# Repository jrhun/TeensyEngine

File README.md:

# TeensyEngine

TeensyEngine is primarily the software I use for my Totem Pole - named *The Orb*. 

Included in this repository is a description of both the hardware and software features, including the MCAD/ECAD designs for everything.
It includes an emulator that's using OpenFrameworks for display and UI control, allowing easy testing and development.

<details>
<summary>  The Orb in the wild 
</summary>

</details>

## Contents 
- [About](#about)
- [Features](#features)
- [Hardware](#hardware)
- [Software](#software)
- [Credit](#credit)

## About
I took ~2000 LED lights and carefully shoved them inside a polycarbonate ball that was then placed on top of a stick and hooked up to a microprocessor and battery pack. Shockingly, it worked quite well! I use it as a Totem Pole for music festivals, come say hi if you see it!

This has been a multiyear endeavor  that I've slowly added more and more features to. It's the 4th iteration of the hardware including LEDs and controller/battery box. The first version was a couple of LEDs taped down inside two salad bowls - [how far this project has come since then!](buildLog/README.md#previous-versions)

Just a heads up - I'm an almost completely self taught programmer/3d modeler/electronics designer, there is a level of *jank* at times that should be expected to come of that, but overall I've been very pleased with the outcome! 
I will gladly take any suggestions or tips to improve my work, please comment any suggestions!

## Features

- 25+ different patterns with the ability to change the colour palette being used for most patterns!
- Custom global blur/fade/glitter effects that can run on top of any pattern
- Text overlay onto patterns with the ability to enter custom text using the controller
- LCD Screen for changing settings/patterns + showing battery voltage and power usage
- Current sensor for monitoring power usage
- Encoder + buttons for navigating the UI
- An accelerometer (because why not)
- Microphone input 
- Wireless compatibility with NRF24L01 or ESP-01

<details open>
<summary> Videos of patterns on the hardware </summary>

https://user-images.githubusercontent.com/25134458/209674595-40512c94-f8f8-4173-94cc-6f29fc267113.mp4

https://user-images.githubusercontent.com/25134458/209741537-4713a7b6-7f0b-4868-8ff8-e278ab186450.mp4

https://user-images.githubusercontent.com/25134458/209743201-d97811d2-97b1-4fea-91a2-2c5a3d3df347.mp4

</details>

## Hardware
Some photos of the completed project can be found [here](buildLog/README.md).
I made a custom circuit board for connecting everything up along with a daughter board for [powering](#Power) the LEDs and providing the data through a CAT5 cable. 

#### Processor
A teensy 4.0 is the heart of the project, providing plenty of raw power to overcome my inefficient coding and push out LEDs while controlling  a UI.

#### Accessories
- Microphone - I can't remember what I'm using, one of the Sparkfun electret autogain boards. 
- NRF24l01 - used to connect wirelessly to LED headbands - allows you to change the patterns/brightness/colour of the headbands!
- ESP-01 - pins to connect to an ESP are broken out but not yet implemented
- ACS712 current sensor in series with the LEDs to measure power usage
- MSGEQ7 - the pinout is there but I haven't ended up using it yet
- ILI9341 colour TFT display 240x320 
- MPU9250 accelerometer

If trying to make this project, please confirm the pinout matches for the display and accelerometer! I got caught out and assumed they were the same for the two almost identical accelerometers I had, then needed to edit the circuit board. Also the linear regulator for the processor 5V line got way too hot so I changed it for a small buck convertor that (roughly) matched it's footprint. To be honest the circuit board could be redone with a teensy 4.1, as soldering the pogo pins to connect to the back of the teensy 4.0 was very tedious. 

#### Lights
Custom 3d printed scaffolding for strips of SK6805-2427 RGB LEDs, to hold them in a spherical shape inside a polycarbonate ball 25cm in diameter. They're held slightly back from the inside of the sphere to help diffuse the lights nicely. The scaffolding press fits together and tolerances were set for my 3d printer - YUMV. They're also held in place under slight compression from the globe. The LED strips are arranged as 30 to a strip with an offset pattern to reduce crowding at the poles, allowing for an effective resolution of 32H x 64W. See the [build details](buildLog/README.md#leds) for photos. 

The lights are from [Aliexpress](https://www.aliexpress.com/item/32818340106.html?spm=a2g0o.order_list.order_list_main.358.679f1802EQyb32), and were chosen for their high density (120/M, 8.33mm pitch) and thin strips (6mm width). 
Lights with a smaller pitch and thinner strip were outrageously expensive at the time I was purchasing LEDs, but have since come down in price somewhat... Version 5 [TBC](https://www.aliexpress.com/item/1005003798198621.html?spm=a2g0o.productlist.main.1.1ec91845yMUVny&algo_pvid=75d3a123-2f4a-48b9-b82f-fbbad28e56ed&algo_exp_id=75d3a123-2f4a-48b9-b82f-fbbad28e56ed-0&pdp_ext_f=%7B%22sku_id%22%3A%2212000028080815414%22%7D&pdp_npi=2%40dis%21AUD%2140.15%2126.11%21%21%21%21%21%40211bf14716719782508633629d0742%2112000028080815414%21sea&curPageLogUid=63plojRdJNp2)?

#### Power
The whole thing is powered by 4x 18650 batteries, I usually carry a spare set of 4x batteries for each night that it's used which usually lasts the night through.
There's a step-down converter in the controller providing 5V for the teensy and accessories. The full battery voltage is sent up to the LEDs where there is a separate step-down convertor. The benefit of the two power supplies is efficiency and stability, having a separate power source for the controller means its voltage doesn't dip when the LEDs draw a bunch of power. It also means I can provide much more power than *most* USB powerbanks, although I do want to try sending 20v from a 100w USB-C powerbank to the LEDs. Further details in the [build section.](buildLog/README.md#power)

## Software
The software include a basic emulator that runs the same UI and pattern software using OpenFrameworks to display the LEDs. 

<details open>
  <summary>Videos of the controller</summary>
 
  https://user-images.githubusercontent.com/25134458/209736586-94fa050d-8a2f-43fb-920e-38acb0f2c6ba.mp4
  
  https://user-images.githubusercontent.com/25134458/209676572-e61da54b-b9a8-4b95-bfd1-fcbd3a2c399e.mp4
  
</details>

### UI Pages
I've tried to organise the UI controls into roughly similar pages. The current battery voltage and current draw is shown in to top right corner, and the current FastLED FPS reading in the bottom right corner. The name of the totem is on the top of the screen, then the current page and a depiction of what page you're on. Joystick left/right changes the page, and up and down to select a setting. Hovering over a setting allows you to change a value with the encoder, or for some settings such as picking a pattern or palette you can press the joystick to enter a menu for that listing options. 

- **Pattern controls**
  - Select desired patterns from the list of patterns
  - Change overall brightness
  - Select a tempo + tap tempo
  - Change the tempo oscillator between square/ramp/sine etc...
  - Trigger ability to change a patterns settings (e.g. trigger different settings for a pattern without making a complete new one, see )
- **Colour controls**
  - Change current palette with a palette preview option
  - Blend amount when changing palette  over - quick or slow blend
  - Change how fast colours from a palette are cycled through
- **Text/FX controls**
  - Add transparent or opaque text over any pattern, or just blink text 
  - Text scroll speed
  - Select the text from a list or enter custom text (12 char max only!)
  - Global blur/fade/glitter effects
- **Wireless controls**
  - Control the wireless headbands I made using NRF24L01 communication
  - Change the pattern/colour/brightness of headbands in range
- **General settings**
  - LCD Backlight/Dither/Colour temp/Accelerometer/Save/load settings

### Adding a new pattern
The basic format for a pattern is a class inheriting from the `_Pattern` class, and should have the name for the pattern passed to it.

A `drawFrame()` function should be provided that is called to run the pattern. You can set the delay in msec for when to draw the next frame by the value you return. It also provides functions that are automatically called when starting or stopping a pattern, and a trigger option. Helper functions for drawing to the LED matrix are in the `gfx` class from `Graphics.h`. Try using `gfx.getColour(uint8_t offset)` for colours because this links in to the palette system. 

Include the code for a new pattern in `src/patterns/PatternController.h`, then add it as a member to the `PatternController` class and include it in the `patternList`
<details>
<summary>Example pattern</summary>
  
#### Blink all LEDs on/off
  ```
  class PatternBlink : public _Pattern {
  public:
    PatternBlink() : _Pattern("Blink") {}
    uint8_t drawFrame() {
      if (++count > 100) {
        count = 0;
        flip != flip;
      }
      if (flip) gfx.fill(gfx.getColour());
      else      gfx.fill(CRGB::Black);
      return returnVal; //default 10, 1000/10 = 100fps
    }
    uint8_t count = 0;
    bool flip = false;
  };
  ```
</details>

## Arduino code
The Teensyduino core was used for compiling and uploading.
`Graphics.h` does all the heavy lifting for helper functions. 

Arduino libraries used:
- [ILI9341_t3n](https://github.com/KurtE/ILI9341_t3n)
- [Encoder](https://github.com/PaulStoffregen/Encoder/blob/master/Encoder.h) from Paul Stroffregen
- [MPU9250](https://github.com/kriswiner/MPU9250) from kriswiner
- [FastLED](https://github.com/FastLED/FastLED)
- [Teensy ADC](https://github.com/pedvide/ADC)
- [RF24](https://github.com/nRF24/RF24)

## PC Emulator 

https://user-images.githubusercontent.com/25134458/209675905-0a1664af-fdfa-492f-b072-93c58537c89a.mp4

#### Requirements 
OpenFrameworks 0.10.1 was used for the graphics, with the ofxGui addon.

Visual Studio 2019 was used for compiling.
At one point I had it compiling on Mac XCode, but I haven't checked if that still works in a while.

<details open>
  <summary>The emulator has keyboard controls for the UI:</summary>
  
  - WASD: joystick up/left/down/right
  - Q/E: encoder rotate clockwise/counter clockwise
  - F: joystick press 
  - space: separate trigger, triggers effect on certain patterns (calls Pattern::Trigger())
  - Home/End/Del/PgDown: change pitch/roll level to emulate accelerometer changes
  - I: add random impulse to accelerometer data
  - 1 through 7: change beat type (RAMP, INVERSE_RAMP, TRIANGLE, SQUARE, SIN, TRIGGER, GATE, AUDIO, AUDIO_AVG, OFF)
</details>

## To-do list
- [ ] Add more photos of the completed totem to the build log
- [ ] More patterns
- [ ] Accelerometer fluid simulation - I've had multiple attempts but it just doesn't look right, a little beyond my abilities currently!
- [ ] More audio responsive patterns/improving audio code
- [ ] More patterns to respond to accelerometer 
- [ ] Make better use of global effects - the LEDs are double buffered but this is only really used for text currently
- [ ] Rotatable 3d view of the totem in the emulator rather than displaying as a flat 2d matrix

## Credit 
This project has taken inspiration from countless different sources. Please see [CONTRIBUTIONS.md](CONTRIBUTIONS.md) for full details.

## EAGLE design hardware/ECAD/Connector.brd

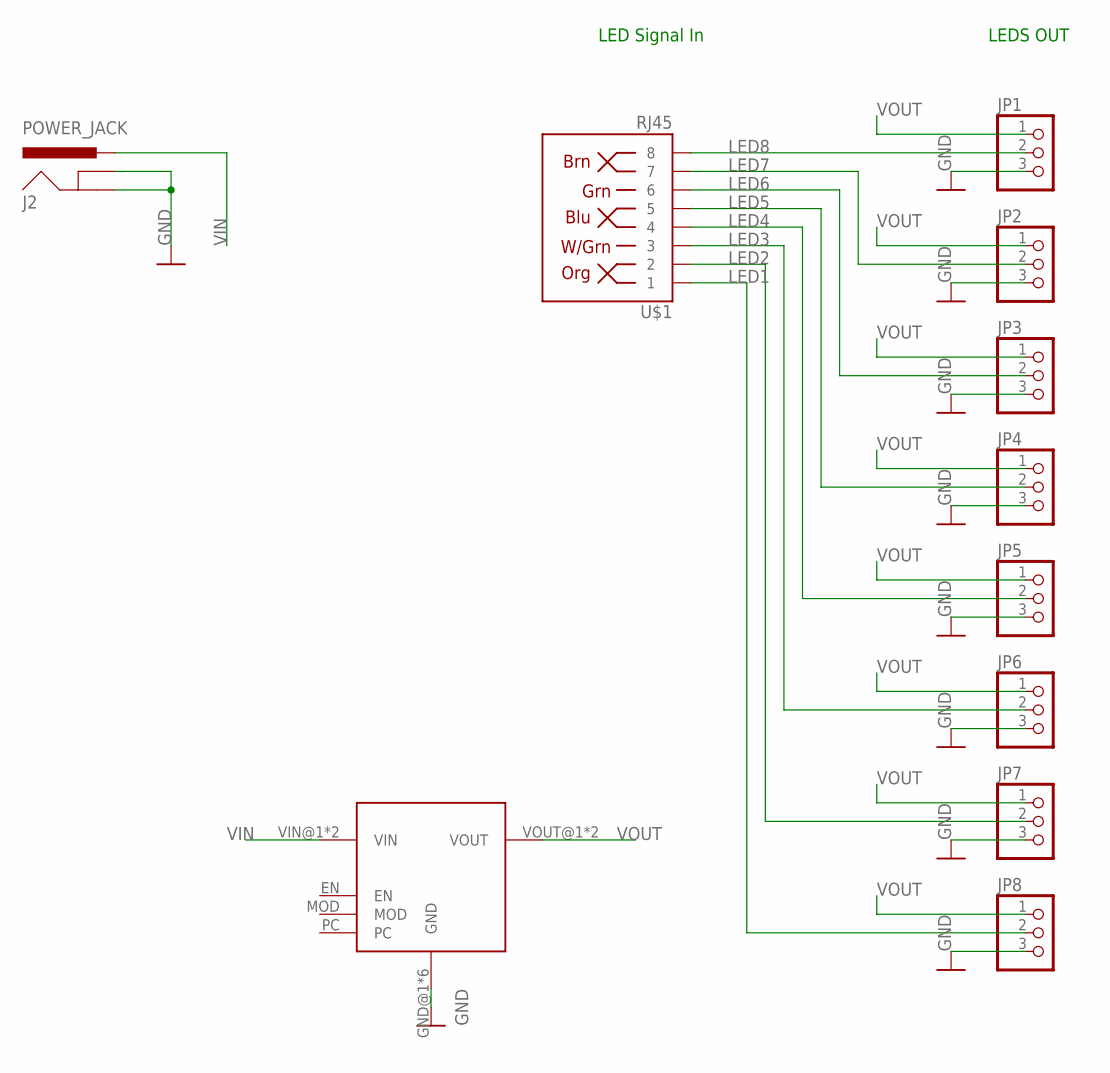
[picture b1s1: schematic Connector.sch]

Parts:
J2: POWER_JACK; POWER_JACK_PTH
JP1, JP2, JP3, JP4, JP5, JP6, JP7, JP8: PINHD-1X3; 1X03
U$1: RJ45; RJ45_WINGS
U$2: 5V-15A-VOLTAGE_CONVERTER; D24V150F

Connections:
GND: J2.GND, J2.GNDBREAK, JP1.3, JP2.3, JP3.3, JP4.3, JP5.3, JP6.3, JP7.3, JP8.3, U$2.GND@1 (GND), U$2.GND@2 (GND), U$2.GND@3 (GND), U$2.GND@4 (GND), U$2.GND@5 (GND), U$2.GND@6 (GND)
LED1: JP8.2, U$1.1
LED2: JP7.2, U$1.2
LED3: JP6.2, U$1.3
LED4: JP5.2, U$1.4
LED5: JP4.2, U$1.5
LED6: JP3.2, U$1.6
LED7: JP2.2, U$1.7
LED8: JP1.2, U$1.8
VIN: J2.PWR, U$2.VIN@1 (VIN), U$2.VIN@2 (VIN)
VOUT: JP1.1, JP2.1, JP3.1, JP4.1, JP5.1, JP6.1, JP7.1, JP8.1, U$2.VOUT@1 (VOUT), U$2.VOUT@2 (VOUT)

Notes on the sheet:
LED Signal In
LEDS OUT

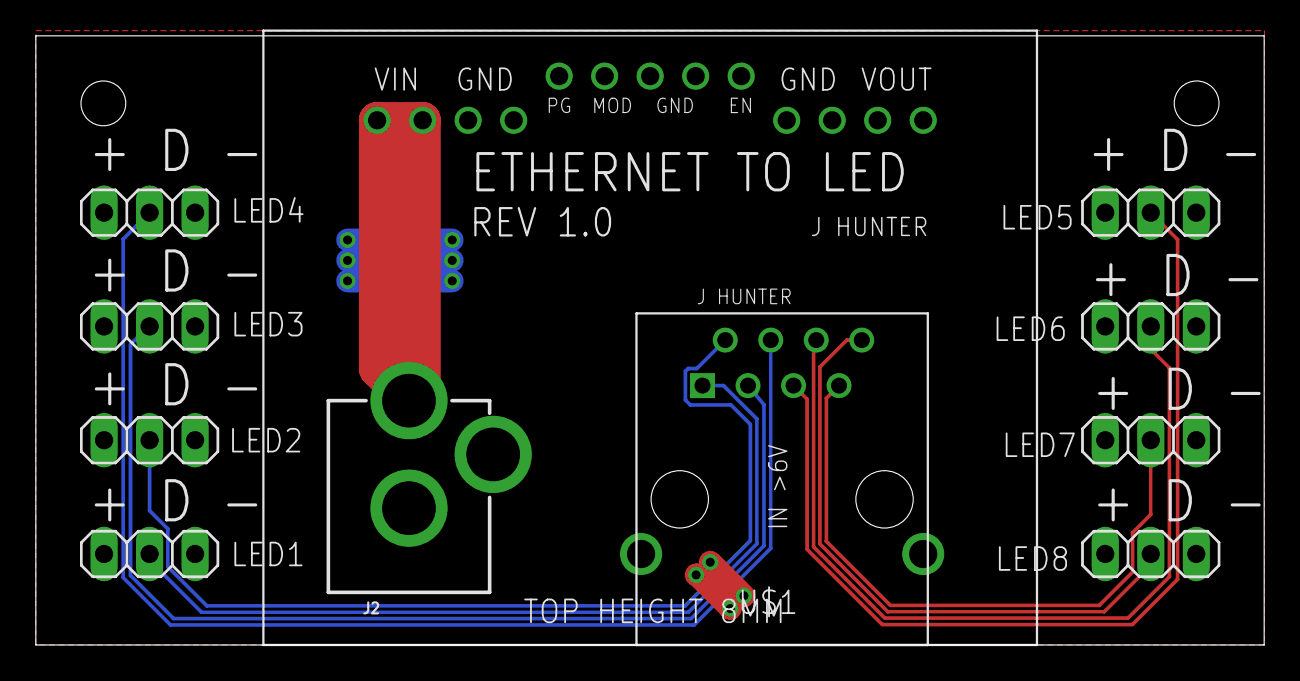
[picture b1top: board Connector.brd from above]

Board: 2 copper layers, 68.6 x 34.0 mm, 11 parts (0 on the bottom side), 11 nets.

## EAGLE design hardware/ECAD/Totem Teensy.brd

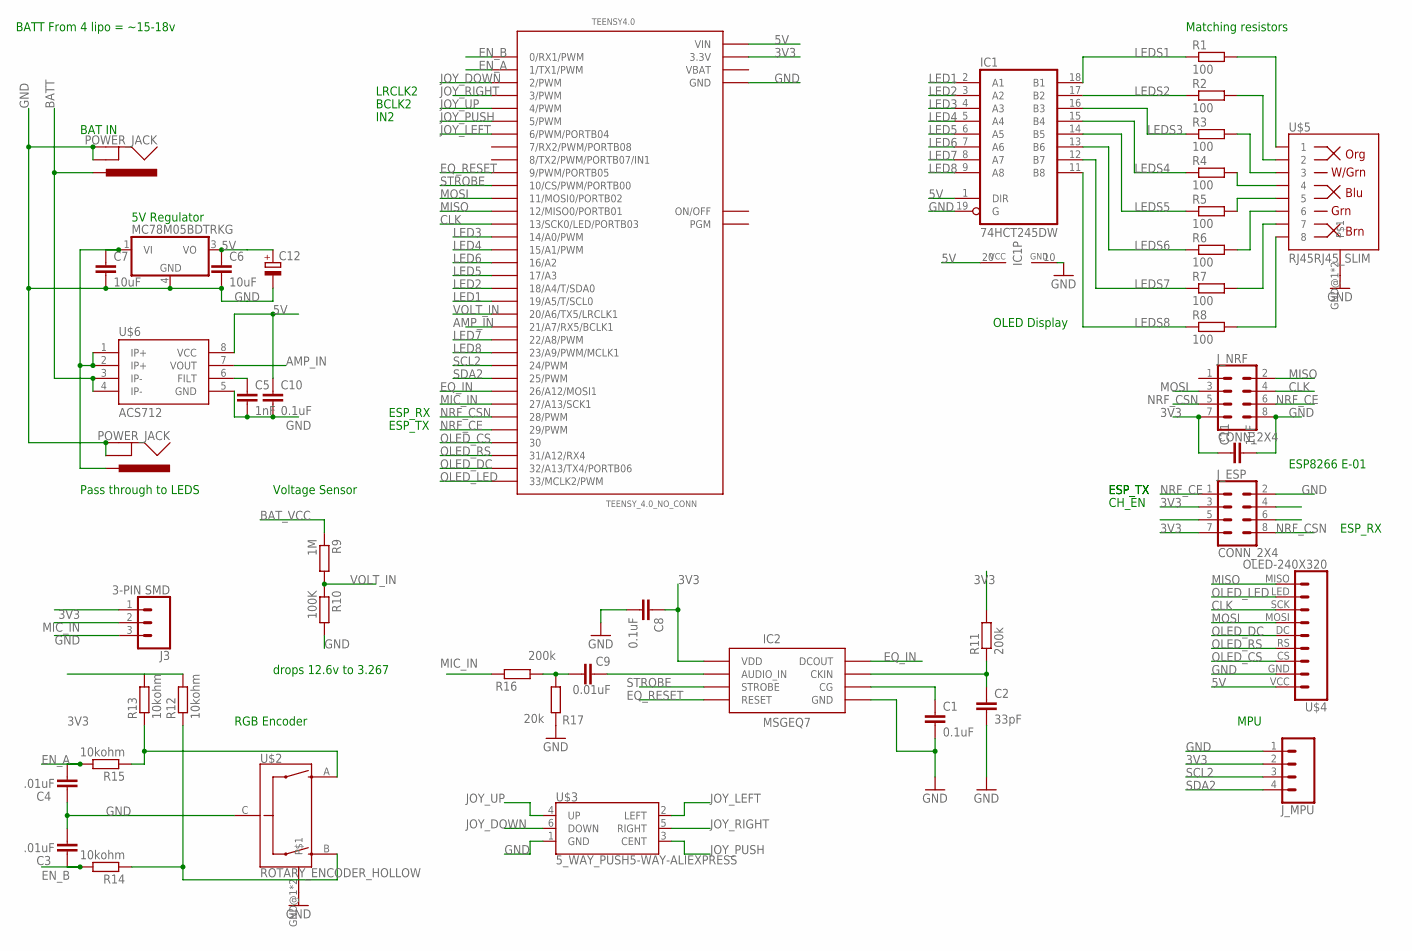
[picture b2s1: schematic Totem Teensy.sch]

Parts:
C1, C8, C10: 0.1uF; C1206
C2: 33pF; C1206
C3, C4: .01uF; C1206
C5: 1nF; C1206
C6, C7: 10uF; C1206
C9: 0.01uF; C1206
C11: 1uF; C1206
C12: CPOL-EUTT2D5L; TT2D5L
IC1: 74HCT245DW; SO20W
IC2: MSGEQ7DIP; DIL08
IC3: MC78M05BDTRKG; DPACK_3
J1, J7: POWER_JACK; POWER_JACK_PTH
J3: 3-PIN SMD; JST-3-SMD
J_ESP: CONN_2X4; 2X4
J_MPU: CONN_04; 1X04
J_NRF: CONN_2X4; 2X4
R1, R2, R3, R4, R5, R6, R7, R8: 100; R1206
R9: 1M; M1206
R10: 100K; M1206
R11, R16: 200k; R1206
R12, R13, R14, R15: 10kohm; R1206
R17: 20k; R1206
TEENSY4.0: TEENSY_4.0_NO_CONN; TEENSY_4.0
U$2: ROTARY_ENCODER_HOLLOW; HOLLOW_ENCODER30R
U$3: 5_WAY_PUSH5-WAY-ALIEXPRESS; 5-WAY_PTH2
U$4: OLED-240X320; OLED_240X320
U$5: RJ45RJ45_SLIM; RJ45_SLIM
U$6: ACS712; SO08

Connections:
3V3: C8.1, C11.1, IC2.1 (VDD), J3.1, J_ESP.3, J_ESP.7, J_MPU.2, J_NRF.7, R11.2, R12.2, R13.2, TEENSY4.0.3.3@0 (3.3V), TEENSY4.0.3.3@1 (3.3V)
5V: C6.1, C10.1, C12.+, IC1.1 (DIR), IC1.20 (VCC), IC3.3 (VO), TEENSY4.0.VIN, U$4.VCC, U$6.8 (VCC)
AMP_IN: TEENSY4.0.21/A7 (21/A7/RX5/BCLK1), U$6.7 (VOUT)
BATT: J1.PWR, U$6.3 (IP-), U$6.4 (IP-)
BAT_VCC: C7.1, IC3.1 (VI), J7.PWR, R9.1, U$6.1 (IP+), U$6.2 (IP+)
CLK: J_NRF.4, TEENSY4.0.13 (13/SCK0/LED/PORTB03), U$4.SCK (CLK)
EN_A: C4.1, R15.2, TEENSY4.0.1 (1/TX1/PWM)
EN_B: C3.2, R14.2, TEENSY4.0.0 (0/RX1/PWM)
EQ_IN: IC2.3 (DCOUT), TEENSY4.0.26 (26/A12/MOSI1)
EQ_RESET: IC2.7 (RESET), TEENSY4.0.9 (9/PWM/PORTB05)
GND: C1.2, C2.2, C3.1, C4.2, C5.2, C6.2, C7.2, C8.2, C10.2, C11.2, C12.-, IC1.10 (GND), IC1.19 (G), IC2.2 (GND), IC3.4 (GND), J1.GND, J1.GNDBREAK, J3.3, J7.GND, J7.GNDBREAK, J_ESP.2, J_MPU.1, J_NRF.8, R10.2, R17.2, TEENSY4.0.GND@0 (GND), TEENSY4.0.GND@1 (GND), TEENSY4.0.GND@2 (GND), U$2.C, U$2.GND@1, U$2.GND@2, U$3.1 (GND), U$4.GND, U$5.GND@1, U$5.GND@2, U$6.5 (GND)
JOY_DOWN: TEENSY4.0.2 (2/PWM), U$3.6 (DOWN)
JOY_LEFT: TEENSY4.0.6 (6/PWM/PORTB04), U$3.2 (LEFT)
JOY_PUSH: TEENSY4.0.5 (5/PWM), U$3.3 (CENT)
JOY_RIGHT: TEENSY4.0.3 (3/PWM), U$3.5 (RIGHT)
JOY_UP: TEENSY4.0.4 (4/PWM), U$3.4 (UP)
LED1: IC1.2 (A1), TEENSY4.0.19/A5 (19/A5/T/SCL0)
LED2: IC1.3 (A2), TEENSY4.0.18/A4 (18/A4/T/SDA0)
LED3: IC1.4 (A3), TEENSY4.0.14/A0 (14/A0/PWM)
LED4: IC1.5 (A4), TEENSY4.0.15/A1 (15/A1/PWM)
LED5: IC1.6 (A5), TEENSY4.0.17/A3
LED6: IC1.7 (A6), TEENSY4.0.16/A2
LED7: IC1.8 (A7), TEENSY4.0.22/A8 (22/A8/PWM)
LED8: IC1.9 (A8), TEENSY4.0.23/A9 (23/A9/PWM/MCLK1)
LEDS1: IC1.18 (B1), R1.1
LEDS2: IC1.17 (B2), R2.1
LEDS3: IC1.16 (B3), R3.1
LEDS4: IC1.15 (B4), R4.1
LEDS5: IC1.14 (B5), R5.1
LEDS6: IC1.13 (B6), R6.1
LEDS7: IC1.12 (B7), R7.1
LEDS8: IC1.11 (B8), R8.1
MIC_IN: J3.2, R16.2, TEENSY4.0.27 (27/A13/SCK1)
MISO: J_NRF.2, TEENSY4.0.12 (12/MISO0/PORTB01), U$4.MISO
MOSI: J_NRF.3, TEENSY4.0.11 (11/MOSI0/PORTB02), U$4.MOSI
unnamed: R1.2, U$5.8 (1)
unnamed: R2.2, U$5.7 (2)
unnamed: R4.2, U$5.5 (4)
unnamed: R3.2, U$5.6 (3)
unnamed: R5.2, U$5.4 (5)
unnamed: R6.2, U$5.3 (6)
unnamed: R7.2, U$5.2 (7)
unnamed: R8.2, U$5.1 (8)
unnamed: C9.2, R16.1, R17.1
unnamed: C9.1, IC2.5 (AUDIO_IN)
unnamed: C5.1, U$6.6 (FILT)
unnamed: R13.1, R15.1, U$2.A
unnamed: R12.1, R14.1, U$2.B
unnamed: C2.1, IC2.8 (CKIN), R11.1
unnamed: C1.1, IC2.6 (CG)
NRF_CE: J_ESP.1, J_NRF.6, TEENSY4.0.29 (29/PWM)
NRF_CSN: J_ESP.8, J_NRF.5, TEENSY4.0.28 (28/PWM)
OLED_CS: TEENSY4.0.30, U$4.CS
OLED_DC: TEENSY4.0.32 (32/A13/TX4/PORTB06), U$4.DC
OLED_LED: TEENSY4.0.33 (33/MCLK2/PWM), U$4.LED
OLED_RS: TEENSY4.0.31 (31/A12/RX4), U$4.RS
SCL2: J_MPU.3, TEENSY4.0.24 (24/PWM)
SDA2: J_MPU.4, TEENSY4.0.25 (25/PWM)
STROBE: IC2.4 (STROBE), TEENSY4.0.10 (10/CS/PWM/PORTB00)
VBAT: TEENSY4.0.VBAT
VOLT_IN: R9.2, R10.1, TEENSY4.0.20/A6 (20/A6/TX5/LRCLK1)

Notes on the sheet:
Matching resistors
RGB Encoder
OLED Display
BATT From 4 lipo = ~15-18v
5V Regulator
Pass through to LEDS
BAT IN
ESP8266 E-01
ESP_TX
ESP_RX
MPU
BCLK2
IN2
LRCLK2
Voltage Sensor
drops 12.6v to 3.267
CH_EN

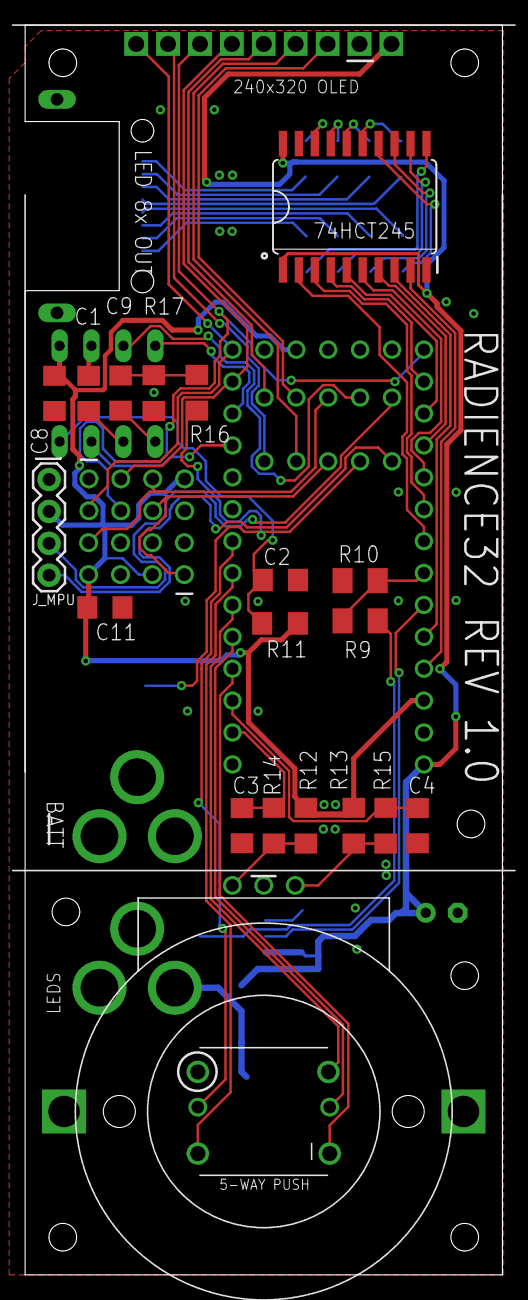
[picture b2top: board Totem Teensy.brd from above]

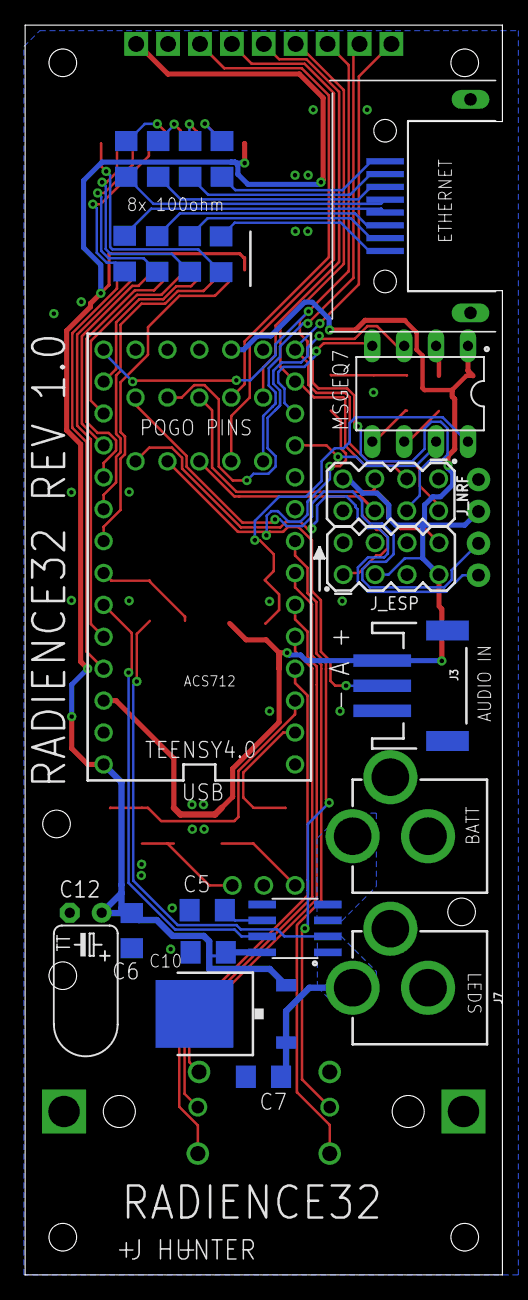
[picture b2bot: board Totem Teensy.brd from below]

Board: 2 copper layers, 38.0 x 99.5 mm, 44 parts (23 on the bottom side), 60 nets.

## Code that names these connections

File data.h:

#ifndef DATA_H
#define DATA_H


// PIN DEFINITIONS
#if defined(ESP32)
#define EN_A_PIN        34
#define EN_B_PIN        35
#define JOY_CENTRE_PIN  22
#define JOY_UP_PIN      15
#define JOY_LEFT_PIN    2
#define JOY_DOWN_PIN    4
#define JOY_RIGHT_PIN   3

#define EQ_RESET_PIN    19
#define EQ_STROBE_PIN   21
#define OLED_LED_PIN    1
#define EQ_AUDIO_PIN    36  // ADC1 CH0
#define AMP_IN_PIN      39

#define OLED_DC 16
#define OLED_RS 17
#define OLED_CS 5

#endif // esp32 defines
// teensy 4.x
#if defined(__IMXRT1052__) || defined(__IMXRT1062__) 
#define EN_A_PIN        1
#define EN_B_PIN        0
#define JOY_CENTRE_PIN  5
#define JOY_UP_PIN      2
#define JOY_LEFT_PIN    6
#define JOY_DOWN_PIN    4
#define JOY_RIGHT_PIN   3

#define EQ_RESET_PIN    9
#define EQ_STROBE_PIN   10
#define EQ_AUDIO_PIN    26  //A12
#define MIC_IN_PIN      27  //A13
#define AMP_IN_PIN      21  //A7
#define VOLTS_IN_PIN    20  //A6

#define NRF_CE_PIN      29
#define NRF_CSN_PIN     28
#define ESP_RX          28 //RX7
#define ESP_TX          29 //TX7

// Normal Connections
#define TFT_DC      32
#define TFT_CS      30
#define TFT_RST     31
#define TFT_BACKLIGHT 33

#define LED1            19
#define LED2            18
#define LED3            14
#define LED4            15
#define LED5            17
#define LED6            16
#define LED7            22
#define LED8            23


// MPU9250 on SCL2/ SDA2

#include <ADC.h>
ADC *adc = new ADC(); 

#endif // teensy 4.x

#define NUM_VARS    6
#define NUM_BUTTONS 6

#ifndef SCREEN_WIDTH
#define SCREEN_WIDTH	64
#endif
#ifndef SCREEN_HEIGHT
#define SCREEN_HEIGHT	32
#endif

#define ARRAY_SIZE(A) (sizeof(A) / sizeof((A)[0]))

#if defined(ARDUINO)
//typedef String String

#else
#include <string>
typedef std::string String;
#define PROGMEM
#endif

// use variable reference for UI functions
// control a variable between min and max values
//template<class TYPE>
class VariableReference {
	typedef uint8_t TYPE;
public:
	VariableReference() : d(NULL), starting(128), min(0), max(0), wrap(true) {}
	VariableReference(const char* name, TYPE *t, TYPE starting = 128, TYPE min = 0, TYPE max = 255, bool wrap = false) : name(name), d(t), starting(starting), min(min), max(max), wrap(wrap) {}

	const char* name;
	String getName() {
		return name;
	}

	String getValue() {
#if defined(ESP32) || defined(CORE_TEENSY)
		return String(*d);
#else
		return to_string(*d);
#endif
	}
	TYPE *d;
	TYPE starting;
	TYPE min;
	TYPE max;
	void(*callback)() = NULL;
	bool wrap;

	void setCallback(void(*fn)()) { callback = fn; }

	void inc(TYPE amount = 1) {
		if (*d + amount > max) {
			if (wrap) 	*d = *d - max + amount;
			else 		*d = max;
		} else {
      *d += amount;
		}
		if (callback) {
			callback();
		}
	}

	void dec(TYPE amount = 1) {
		if (*d - amount < min) {
			if (wrap) 	*d = *d - amount + max; // works for both signed/unsigned + floats
			else		*d = min;
		}
		else			*d -= amount;
		if (callback) {
			callback();
		}
	}

	TYPE& operator * (void) {
		return *d;
	}

// TYPE& operator & (void) {
//   return *d;
//  }

};

namespace Data {
	//  public:
	// VARS

	// Led control variables
	uint8_t brightness = 24;
	uint8_t fadeAmount = 48;
	bool adjustGamma = false;

	VariableReference brightness_t("Brightness", &brightness, 24);

	uint8_t hueScale = 3;
	uint8_t hueInc = 1;
	uint16_t hue = 0;
	bool hueChange = true;
	uint8_t hueSpeed = 30;
	uint8_t getHue() {
		return hue / hueScale;
	}
	void incHue() {
		hue = (hue + hueInc) % (256 * hueScale);
	}

	//pattern vars
	uint8_t FPS = 90;

	// UI variables
	uint8_t currentPattern = 0;

 
	uint8_t paletteIndex = 0;
  uint8_t hbPaletteIndex = 0;
  uint8_t changePaletteDelay = 0; //seconds

  uint32_t colorTemp = 0;




	// audio vars
  bool audioOn = false;
	uint8_t noiseFloor = 65;
  uint8_t audioThreshold = 128;
  float beat = 0;

  uint8_t maxVol = 40;

  const uint8_t numSamples = 16;
  uint16_t sampleArray[numSamples];
  uint16_t sampleSum = 0;
  uint16_t sampleAvg = 0;
  uint16_t sampleCount = 0;
  uint8_t samplePeak = 0;
  float samplePeakVal = 0.0f;
  unsigned long peakTime;


  // backlight
  uint8_t backlight_brightness = 63;
  VariableReference backlight_t{"Backlight", &backlight_brightness, 63, 0, 63};
  
  uint8_t triggerType = 0;
  VariableReference triggerType_t{"Trigger", &triggerType, 4, 0, 6};

  
  //text
  bool textOn = false;
  uint8_t scrollSpeed = 1;
  uint8_t textIndex = 0;
  const uint8_t textOptionsCount = 17; // custom options at index 15 and 16
  const uint8_t customIndex1 = textOptionsCount-2;
  const uint8_t customIndex2 = textOptionsCount-1;
  VariableReference textIndex_t{"Text", &textIndex, 0, 0, textOptionsCount};
  const String textOptions[textOptionsCount] = {
    "Dance!",
    "Floodlight",
    "Good job!",
    "Well done!",
    "Good tune!", 
    "Tune!",
    "Nice one!", 
    "Thanks!",
    "Yew!",
    "Wow!", 
    "Boot!",
    "Love it!",
    "Kick it!", 
    "Hi Mum!",
    "Nailed it!",
    "Custom 1",
    "Custom 2"
  };

  char custom1[12] = "           ";
  char custom2[12] = "           ";

  //accelerometer
  bool MPUOn = false;
  float ax = 9.8f, ay = 0.0f, az = 0.0f;
//  float gx = 0.0f, gy = 0.0f, gz = 0.0f;
  float pitch = 30.0f;
  float roll = 0.0f;

  //headbands
  enum {hbPaletteUpdate = 1, hbBrightnessUpdate, hbPatternUpdate}; // update type
  uint8_t sendUpdate = 0;

  bool hbOn = true;
  bool hbManual = false;
  bool hbFade = false;
  bool hbSendUpdate = true;
  bool syncHue = true;//not used
  uint16_t hbSendMillisDelay = 100;
  uint8_t indexSkip = 1;
  uint8_t hbHueOffset = 50;
  uint8_t hbHueDelay = 16;
  uint8_t hbIndex = 0;
  uint8_t hbSpeed = 50;
  uint8_t hbBrightness = 128;
  uint8_t hbFadeAmount = 32;
  uint8_t hbCurrentPattern = 2;
  const uint8_t hbMaxPatterns = 6;
  const String hbPatternNames[hbMaxPatterns] = { 
    "Wipe Colours", 
    "Rotate Colours", 
    "Rotate Colours2", 
    "Sparkles", 
    "Commets", 
    "Solid colour",
  };

  VariableReference brightnessHb_t("Brightness", &hbBrightness, hbBrightness, 0, 255);
  VariableReference fadeHb_t("Fade", &hbFadeAmount, hbFadeAmount, 0, 128);
  VariableReference speedHb_t("Speed", &hbSpeed, hbSpeed, 0, 255);
  VariableReference hueDelayHb_t("Hue delay", &hbHueDelay, hbHueDelay, 1, 64);

//  VariableReference hbPattern_t{"HB Pattern", &hbCurrentPattern, 2, 0, hbMaxPatterns};

  bool syncPalettes = false;

  bool dither = false;
  bool accelerometer = true;


} //end nameSpace Data


//temp vars for checking out different settings 
float GuiVars1 = 0.6; //1.6, 0.6 1.25, 0.87, 1.25, 1.15
float GuiVars2 = 1.0;
float GuiVars3 = 1;
float GuiVars4 = 0.1;
float GuiVars5 = 0.2;
float GuiVars6 = 1.5;
uint8_t FxFade = 128;
uint8_t FxBlur = 0;
uint8_t FxSpiral = 0;
uint8_t FxNoiseSmear = 0;


uint8_t vars[NUM_VARS] = {
  7, 25, 4, 1, 1, 0
};

//uint8_t *speed = &vars[0];
//uint8_t *scale = &vars[1];

String varsName[NUM_VARS] = {
  "Speed", "Scale", "palette", "var4", "var5", "var6"
};


bool buttons[NUM_BUTTONS] = { 0, 1, 1, 1, 0, 0 }; // gamma, dither, on









//gamma LUT
static const uint8_t PROGMEM
gamma5[] = {
  0x00, 0x01, 0x02, 0x03, 0x05, 0x07, 0x09, 0x0b,
  0x0e, 0x11, 0x14, 0x18, 0x1d, 0x22, 0x28, 0x2e,
  0x36, 0x3d, 0x46, 0x4f, 0x59, 0x64, 0x6f, 0x7c,
  0x89, 0x97, 0xa6, 0xb6, 0xc7, 0xd9, 0xeb, 0xff
};
static const uint8_t PROGMEM
gamma6[] = {
  0x00, 0x01, 0x02, 0x03, 0x04, 0x05, 0x06, 0x08,
  0x09, 0x0a, 0x0b, 0x0d, 0x0e, 0x10, 0x12, 0x13,
  0x15, 0x17, 0x19, 0x1b, 0x1d, 0x20, 0x22, 0x25,
  0x27, 0x2a, 0x2d, 0x30, 0x33, 0x37, 0x3a, 0x3e,
  0x41, 0x45, 0x49, 0x4d, 0x52, 0x56, 0x5b, 0x5f,
  0x64, 0x69, 0x6e, 0x74, 0x79, 0x7f, 0x85, 0x8b,
  0x91, 0x97, 0x9d, 0xa4, 0xab, 0xb2, 0xb9, 0xc0,
  0xc7, 0xcf, 0xd6, 0xde, 0xe6, 0xee, 0xf7, 0xff
};


static const uint8_t PROGMEM
decayData[] = {
	0,0,0,0,0,0,0,0,
	0,0,0,0,0,0,1,1,
	1,1,1,1,1,1,2,2,
	2,2,2,3,3,4,4,5,
	5,6,7,8,9,10,11,13,
	14,16,18,21,24,27,30,35,
	39,44,50,57,64,73,83,94,
	106,120,136,155,175,199,225,255
};

uint8_t decayExp(uint8_t i) {
	uint8_t d = i / 4;
	uint8_t r = i % 4; //0 1 2 3
	if (d == 63)
		return decayData[d];// *r + decayData[d - 1] * (3 - r);
	return (decayData[d] * (3 - r) + decayData[d + 1] * r) / 3;
}




#endif //DATA_H

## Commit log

2019-08-19 Add .gitignore and .gitattributes.
2019-08-19 Add project files.
2019-08-20 Init
2019-08-21 SmoothColor
    SmoothColor shader working on both teensy and VS
2019-08-21 Parabolid rendering working
2019-08-22 Cube Spin
2019-08-22 Update TeensyEngine.ino
    type
2019-08-22 Changed to fastled CRGB for color
2019-08-22 Further Changes to use fastled CRGB for color. Also changed to run everything from patternController
2019-08-22 cleaned up some comments
2019-08-22 working on arduino
2019-08-23 Fixed wrap around for cube
2019-08-23 super sampling tests - too much extra memory
2019-08-23 added GUI
2019-08-23 Wireframe
2019-08-29 Updated patterns - changed to global effects
2019-08-29 3d ParticleSystem added
2019-08-30 New pattern testing particles
2019-08-30 Added fire and updated particle pattern
2019-09-04 Added supershape pattern
2019-09-04 Added noise
2019-09-05 Raymarcher added
2019-09-10 added pictures pattern
2019-09-19 Added menu
2019-09-20 Menu updates + test pattern for numbering strips
2019-09-20 updated return FPS
2019-09-29 new pattern
2019-09-30 New patterns added palettes initial - needs work still
2019-10-01 Updated to work on mac
2019-10-01 wave update
    looks more like a tornado
2019-10-01 ignore xcode files
2019-10-02 adding beat to patterns
2019-10-03 var control and trigger rework
2019-10-04 Added Trigger and tap tempo
2019-10-05 FFT tests
2019-10-05 analogIn tests
2019-10-06 more tests
2019-10-06 hmmmmmmmm
2019-10-06 tests
2019-10-06 tests with ads
2019-10-07 UI on teensy
2019-10-09 Updating UI
2019-10-10 Added palettes and changed gfx.getColour to use palettes
2019-10-10 More work on palettes
2019-10-10 Purple rain and particles
2019-10-19 purpleRain and async UI DMA updates
2019-11-01 Updated patterns and fixed menu
2019-11-03 Added headband control
2019-11-11 minor updates and references
2019-11-15 Fixed patterns to use centralised blur. Added volts + amp sensing
2019-11-21 new patters
2019-12-01 custom text and palette preview
2019-12-05 Text display
2019-12-09 Alpha to text, fixed fx for patterns
2019-12-09 trying to add pitch/roll control
2019-12-10 Added water ish accelerometer aware pattern
2019-12-11 fish pattern
2019-12-11 fix floor
    i.e limit amount particle can fall & add some bounce when hitting floor
2019-12-11 updated menu
    option for automatic cycling through palettes
    option for hue change speed
2019-12-12 fixes
2019-12-12 glitter
2019-12-12 edits for teensy compiling
2019-12-12 fixed glitter
2019-12-12 updated patterns
2019-12-12 final edits prior meredith!
2019-12-17 adding hardware details
2019-12-27 reference for pictures
2020-03-09 gp edits, work on audio and minor fixes
2022-11-03 working on it again
2022-11-05 fixed volt/amp measurements. added mario images
2022-11-05 Mario pattern
2022-11-05 fire changes
2022-11-05 fire fixed on pc
2022-11-07 Face pattern complete
2022-11-08 flower pattern start
2022-11-08 flower with rotate
2022-11-08 flowers almost completed - added roses and tulips
2022-11-08 flower complete, refactored slightly for arduino
2022-11-09 blur bug squashed!
2022-11-10 made eyes more narrow
2022-11-10 even more narrow
2022-11-10 more narrow! and fixed eye movements
2022-11-25 changed eyePos
2022-11-25 fluidsim basic, similar to noita
2022-11-25 sand method
2022-11-26 new water attempt
2022-11-28 fixed force from accel
2022-12-01 lavaLamp
2022-12-01 lavalamp init
2022-12-01 improvements to lavaLamp
2022-12-02 lavalamp working pretty well
2022-12-25 Pre-Meredith Edits
2022-12-26 adding comments
2022-12-26 Organisation
2022-12-27 comments
2022-12-27 rename
2022-12-27 added build info
2022-12-27 change png
2022-12-27 change formats
2022-12-27 format
2022-12-27 remove
2022-12-28 typos
2023-12-07 new pattern mushroom
2024-03-20 Added 3d model files
    fusion360 + unchecked step format, recommend to use fusion 360 to isolate and print parts
2024-03-20 totem controller 3d files
    fusion 3d files for controller
2024-03-20 Delete Totem_Teensy v24.f3z
    old version, moved correct to right folder

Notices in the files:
parts and their libraries:
SparkFun-Connectors: Licensing: Creative Commons ShareAlike 4.0 International - https://creativecommons.org/licenses/by-sa/4.0
